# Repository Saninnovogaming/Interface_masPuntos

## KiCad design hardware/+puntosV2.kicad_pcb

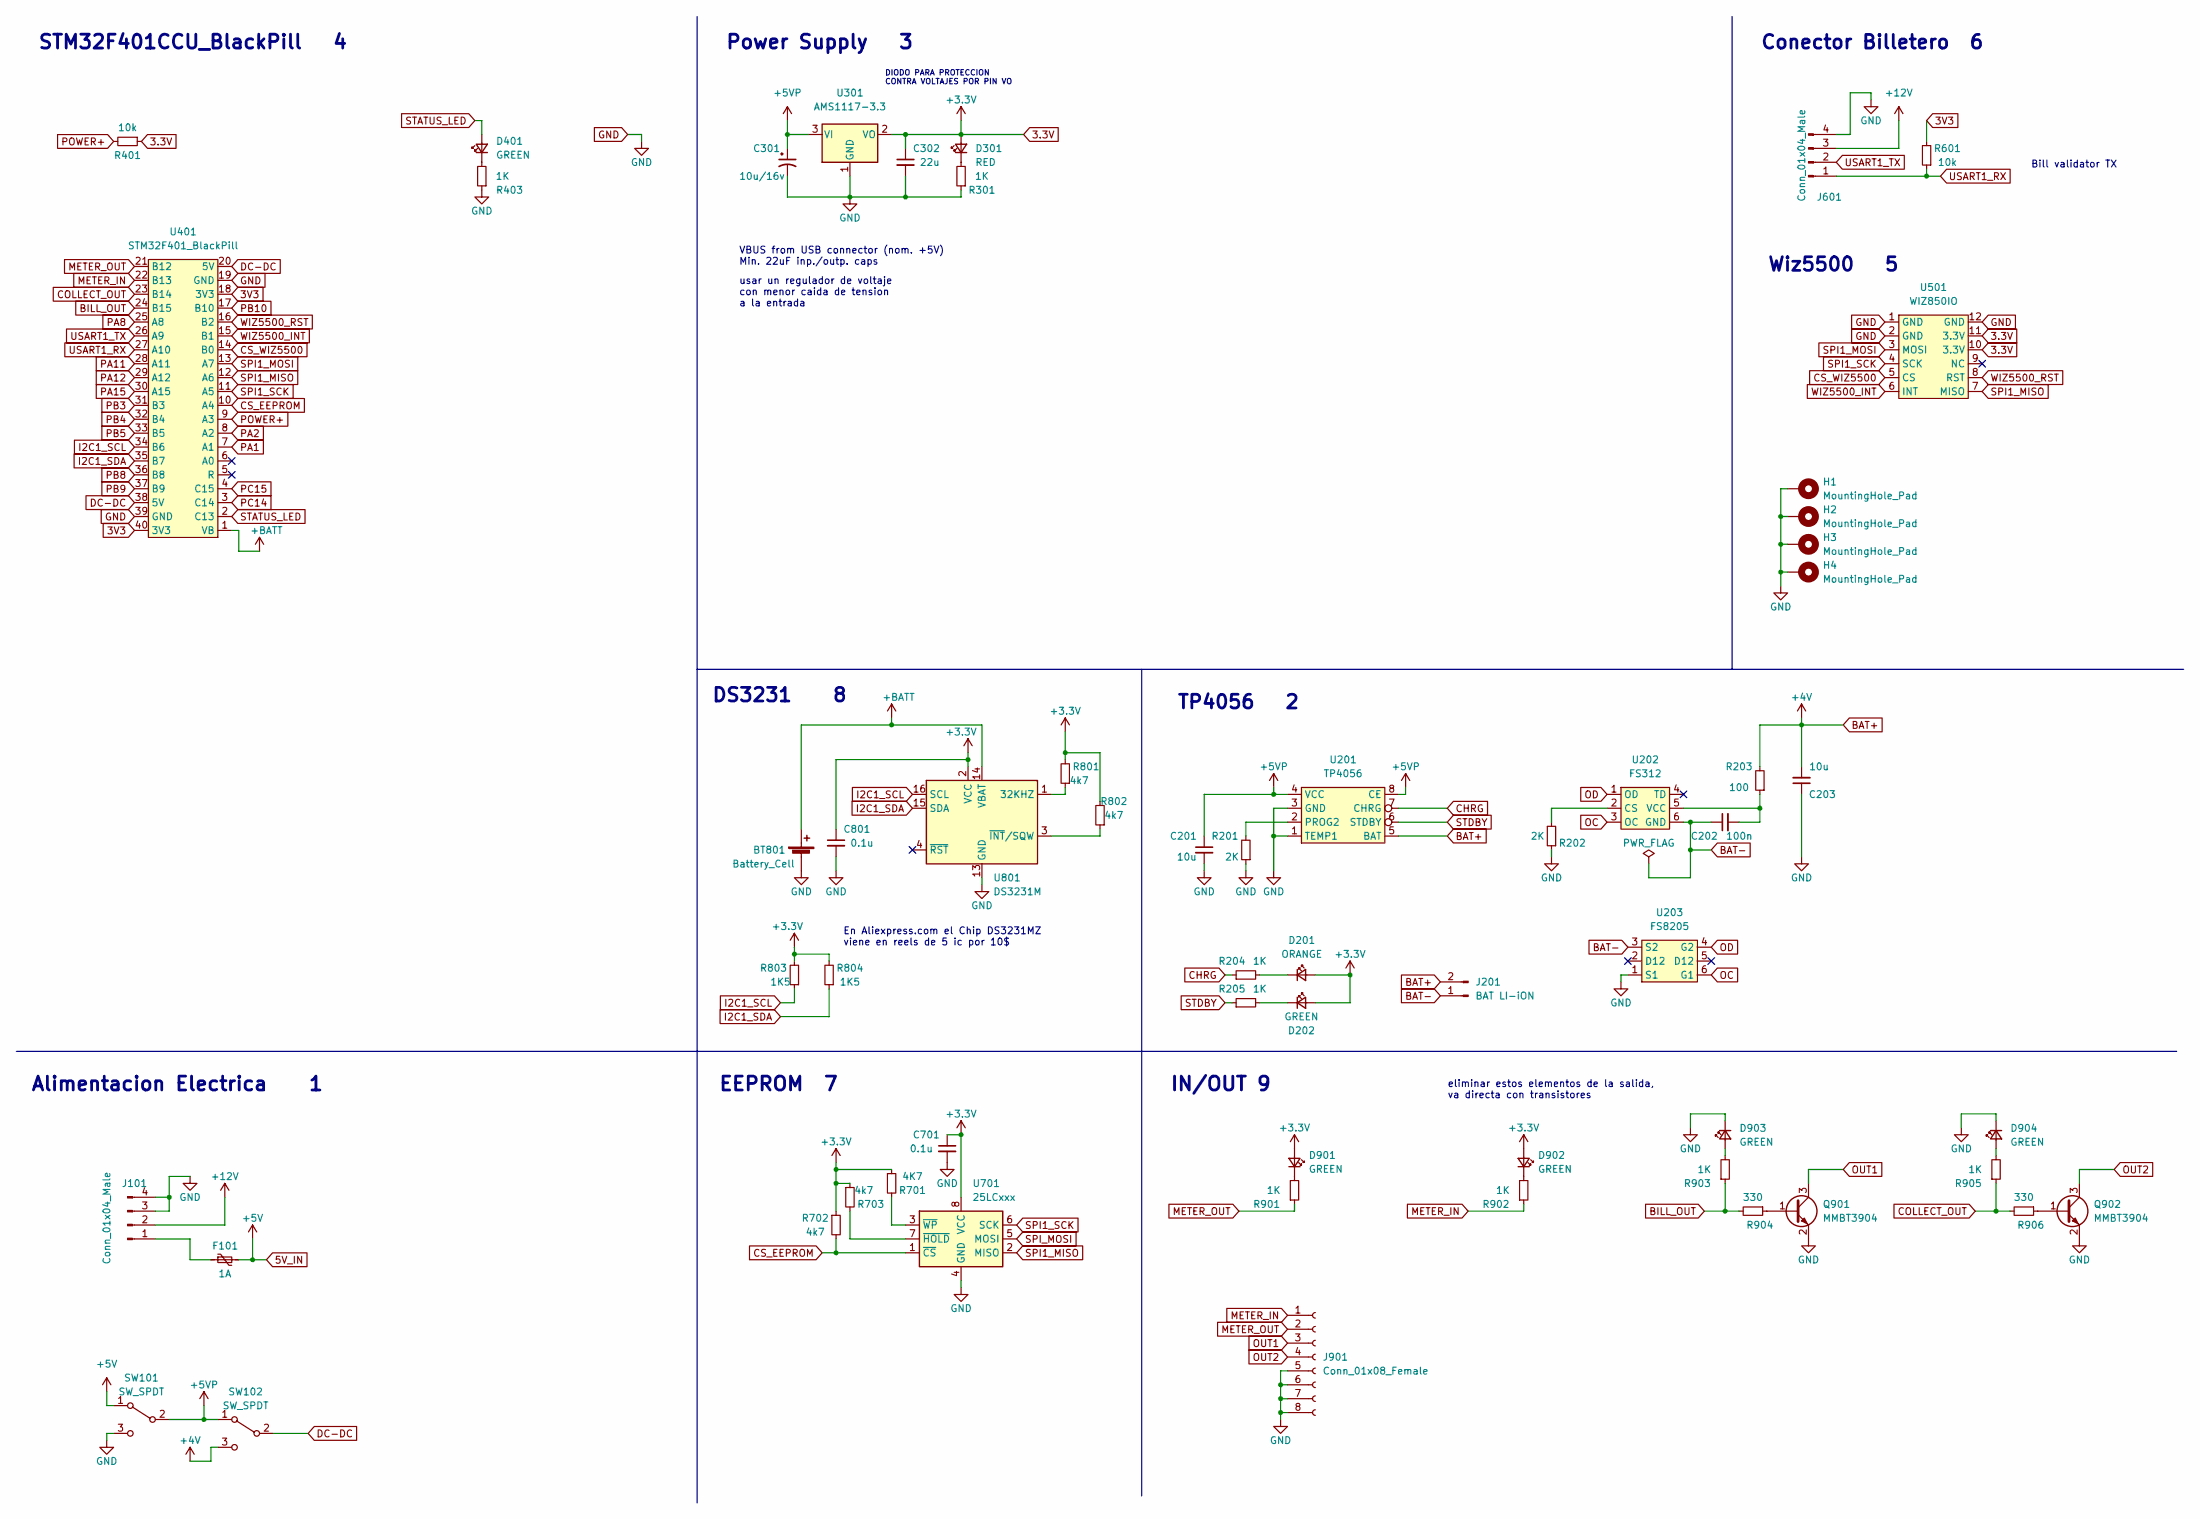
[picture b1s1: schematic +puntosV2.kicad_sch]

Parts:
BT801: Battery_Cell; cr1220
C201, C203: 10u; C_0805_2012Metric; LCSC Part # C40894
C202: 100n; C_0402_1005Metric; LCSC Part # C1525
C301: 10u/16v; CP_EIA-3216-18_Kemet-A
C302: 22u; C_0805_2012Metric; LCSC Part # C129303
C701, C801: 0.1u; C_0805_2012Metric; LCSC Part # C40894
D201: ORANGE; LED_0603_1608Metric; LCSC Part # C375574
D202, D401, D901, D902, D903, D904: GREEN; LED_0603_1608Metric; LCSC Part # C375574
D301: RED; LED_0603_1608Metric; LCSC Part # C375573
F101: 1A; Fuse_1206_3216Metric; LCSC Part # C71465
H1: MountingHole_Pad; MountingHole_2.2mm_M2_Pad_Via
H2, H3, H4: MountingHole_Pad; MountingHole_2.7mm_Pad_Via
J101, J601: Conn_01x04_Male; Molex_Mini-Fit_Jr_5566-04A
J201: BAT LI-iON; BatteryHolder_MPD_BH-18650-PC2; LCSC Part # C238063
J901: Conn_01x08_Female; molex_Mini-Fit_Jr_5566-08A
Q901, Q902: MMBT3904; SOT-23; LCSC Part # C2150
R201, R202: 2K; R_0603_1608Metric; LCSC Part # C105576
R203: 100; R_0402_1005Metric; LCSC Part # C106233
R204, R205, R301, R403, R901, R902, R903, R905: 1K; R_0402_1005Metric; LCSC Part # C25867
R401: 10k; R_0402_1005Metric; LCSC Part # C25744
R601: 10k; R_0402_1005Metric; LCSC Part # C144754
R701: 4K7; R_0402_1005Metric; LCSC Part # C105871
R702, R703, R801, R802: 4k7; R_0402_1005Metric; LCSC Part # C105871
R803, R804: 1K5; R_0402_1005Metric; LCSC Part # C25867
R904, R906: 330; R_0402_1005Metric; LCSC Part # C105876
SW101, SW102: SW_SPDT; SLIDE SWITCH VERTICAL SMD
U201: TP4056; SOP-8-1EP_4.57x4.57mm_P1.27mm_EP4.57x4.45mm_ThermalVias
U202: FS312; TSOT-23-6_HandSoldering
U203: FS8205; TSOT-23-6_HandSoldering
U301: AMS1117-3.3; SOT-223-3_TabPin2; LCSC Part # C6186
U401: STM32F401_BlackPill
U501: WIZ850IO
U701: 25LCxxx; SOIC-8_3.9x4.9mm_P1.27mm
U801: DS3231M; SOIC-16W_7.5x10.3mm_P1.27mm

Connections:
3.3V: C302.1, C701.1, C801.1, D201.2 (A), D202.2 (A), D301.2 (A), D901.2 (A), D902.2 (A), R401.1, R701.1, R702.1, R703.1, R801.2, R802.2, R803.2, R804.2, U301.2 (VO), U501.10 (3.3V), U501.11 (3.3V), U701.8 (VCC), U801.2 (VCC)
3V3: R601.2, U401.18 (3V3), U401.40 (3V3)
5V_IN: F101.2, SW101.1 (A)
+5VP: C201.1, C301.1, SW101.2 (B), SW102.1 (A), U201.4 (VCC), U201.8 (CE), U301.3 (VI)
+12V: J101.2, J601.3
+BATT: BT801.1 (+), U401.1 (VB), U801.14 (VBAT)
BAT+: C203.2, J201.2, R203.2, SW102.3 (C), U201.5 (BAT)
BAT-: C202.1, J201.1, U202.6 (GND), U203.3 (S2)
BILL_OUT: R903.1, R904.2, U401.24 (B15)
CHRG: R204.1, U201.7 (CHRG)
COLLECT_OUT: R905.1, R906.2, U401.23 (B14)
CS_EEPROM: R702.2, U401.10 (A4), U701.1 (~CS)
CS_WIZ5500: U401.14 (B0), U501.5 (CS)
DC-DC: SW102.2 (B), U401.20 (5V), U401.38 (5V)
GND: BT801.2 (-), C201.2, C203.1, C301.2, C302.2, C701.2, C801.2, D903.1 (K), D904.1 (K), H1.1, H2.1, H3.1, H4.1, J101.3, J101.4, J601.4, J901.5, J901.6, J901.7, J901.8, Q901.2 (E), Q902.2 (E), R201.1, R202.1, R301.1, R403.1, SW101.3 (C), U201.1 (TEMP1), U201.3 (GND), U203.1 (S1), U301.1 (GND), U401.19 (GND), U401.39 (GND), U501.1 (GND), U501.2 (GND), U501.12 (GND), U701.4 (GND), U801.5 (GND), U801.6 (GND), U801.7 (GND), U801.8 (GND), U801.9 (GND), U801.10 (GND), U801.11 (GND), U801.12 (GND), U801.13 (GND)
I2C1_SCL: R803.1, U401.34 (B6), U801.16 (SCL)
I2C1_SDA: R804.1, U401.35 (B7), U801.15 (SDA)
METER_IN: J901.1, R902.1, U401.22 (B13)
METER_OUT: J901.2, R901.1, U401.21 (B12)
unnamed: C202.2, R203.1, U202.5 (VCC)
unnamed: D201.1 (K), R204.2
unnamed: D202.1 (K), R205.2
unnamed: D301.1 (K), R301.2
unnamed: D401.1 (K), R403.2
unnamed: D901.1 (K), R901.2
unnamed: D902.1 (K), R902.2
unnamed: D903.2 (A), R903.2
unnamed: D904.2 (A), R905.2
unnamed: F101.1, J101.1
unnamed: Q901.1 (B), R904.1
unnamed: Q902.1 (B), R906.1
unnamed: R201.2, U201.2 (PROG2)
unnamed: R202.2, U202.2 (CS)
unnamed: R701.2, U701.3 (~WP)
unnamed: R703.2, U701.7 (~HOLD)
unnamed: R801.1, U801.1 (32KHZ)
unnamed: R802.1, U801.3 (~INT/SQW)
OC: U202.3 (OC), U203.6 (G1)
OD: U202.1 (OD), U203.4 (G2)
OUT1: J901.3, Q901.3 (C)
OUT2: J901.4, Q902.3 (C)
PA1: U401.7 (A1)
PA2: U401.8 (A2)
PA8: U401.25 (A8)
PA11: U401.28 (A11)
PA12: U401.29 (A12)
PA15: U401.30 (A15)
PB3: U401.31 (B3)
PB4: U401.32 (B4)
PB5: U401.33 (B5)
PB8: U401.36 (B8)
PB9: U401.37 (B9)
PB10: U401.17 (B10)
PC14: U401.3 (C14)
PC15: U401.4 (C15)
POWER+: R401.2, U401.9 (A3)
SPI1_MISO: U401.12 (A6), U501.7 (MISO), U701.2 (MISO)
SPI1_MOSI: U401.13 (A7), U501.3 (MOSI)
SPI1_SCK: U401.11 (A5), U501.4 (SCK), U701.6 (SCK)
SPI_MOSI: U701.5 (MOSI)
STATUS_LED: D401.2 (A), U401.2 (C13)
STDBY: R205.1, U201.6 (STDBY)
USART1_RX: J601.1, R601.1, U401.27 (A10)
USART1_TX: J601.2, U401.26 (A9)
WIZ5500_INT: U401.15 (B1), U501.6 (INT)
WIZ5500_RST: U401.16 (B2), U501.8 (RST)

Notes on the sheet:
Conector Billetero 6
DIODO PARA PROTECCION CONTRA VOLTAJES POR PIN VO
eliminar estos elementos de la salida, va directa con transistores
DS3231 8
usar un regulador de voltaje con menor caida de tension a la entrada
Alimentacion Electrica 1
IN/OUT 9
En Aliexpress.com el Chip DS3231MZ viene en reels de 5 ic por 10$
Power Supply 3
STM32F401CCU_BlackPill 4
EEPROM 7
Wiz5500 5
TP4056 2
VBUS from USB connector (nom. +5V) Min. 22uF inp./outp. caps
Bill validator TX

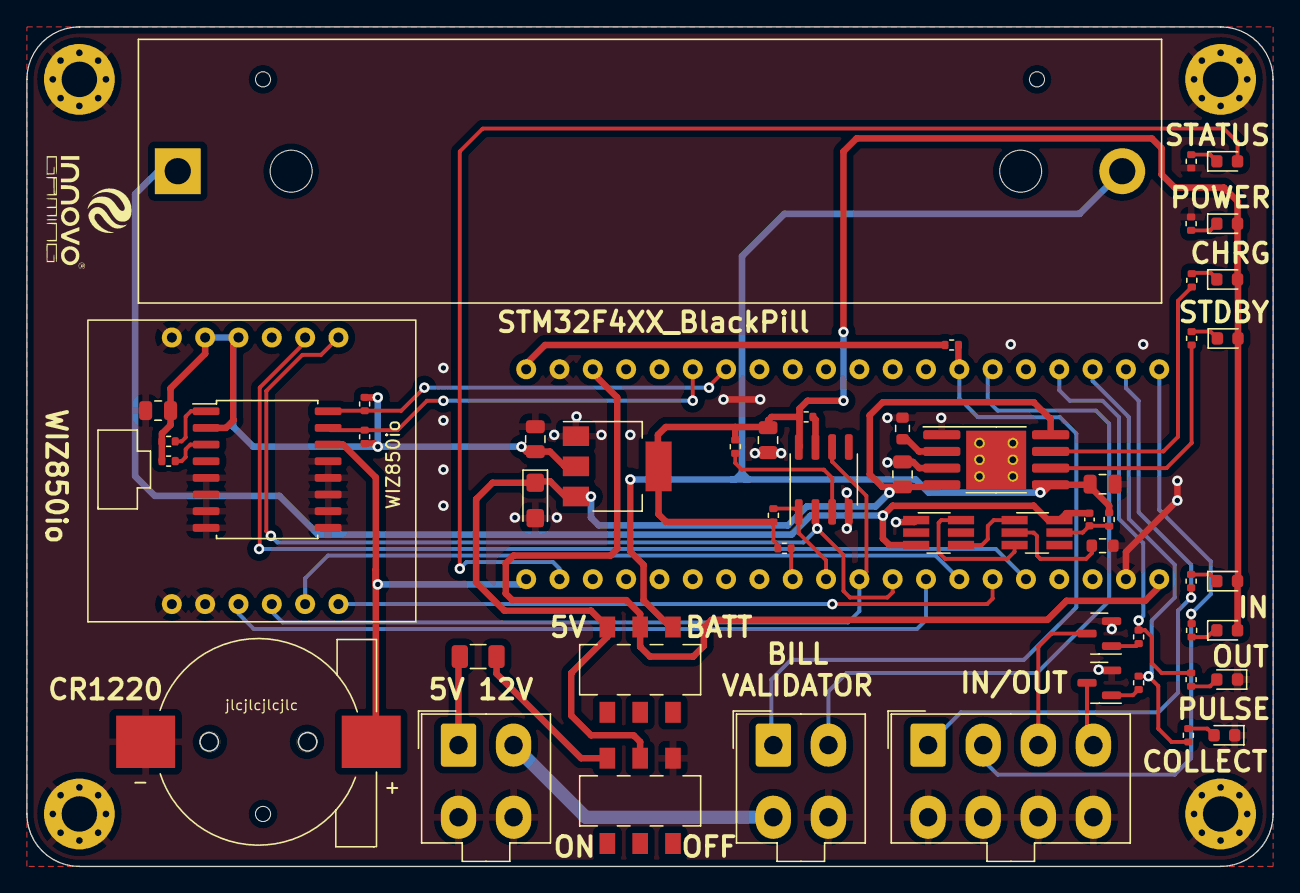
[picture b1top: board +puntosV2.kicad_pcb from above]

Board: 2 copper layers, 95.0 x 64.0 mm, 59 parts (0 on the bottom side), 51 nets.

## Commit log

2022-11-02 add the hardware and software initial documents
2022-11-02 Make order of the SSP library
2022-11-02 add .gitignore file
